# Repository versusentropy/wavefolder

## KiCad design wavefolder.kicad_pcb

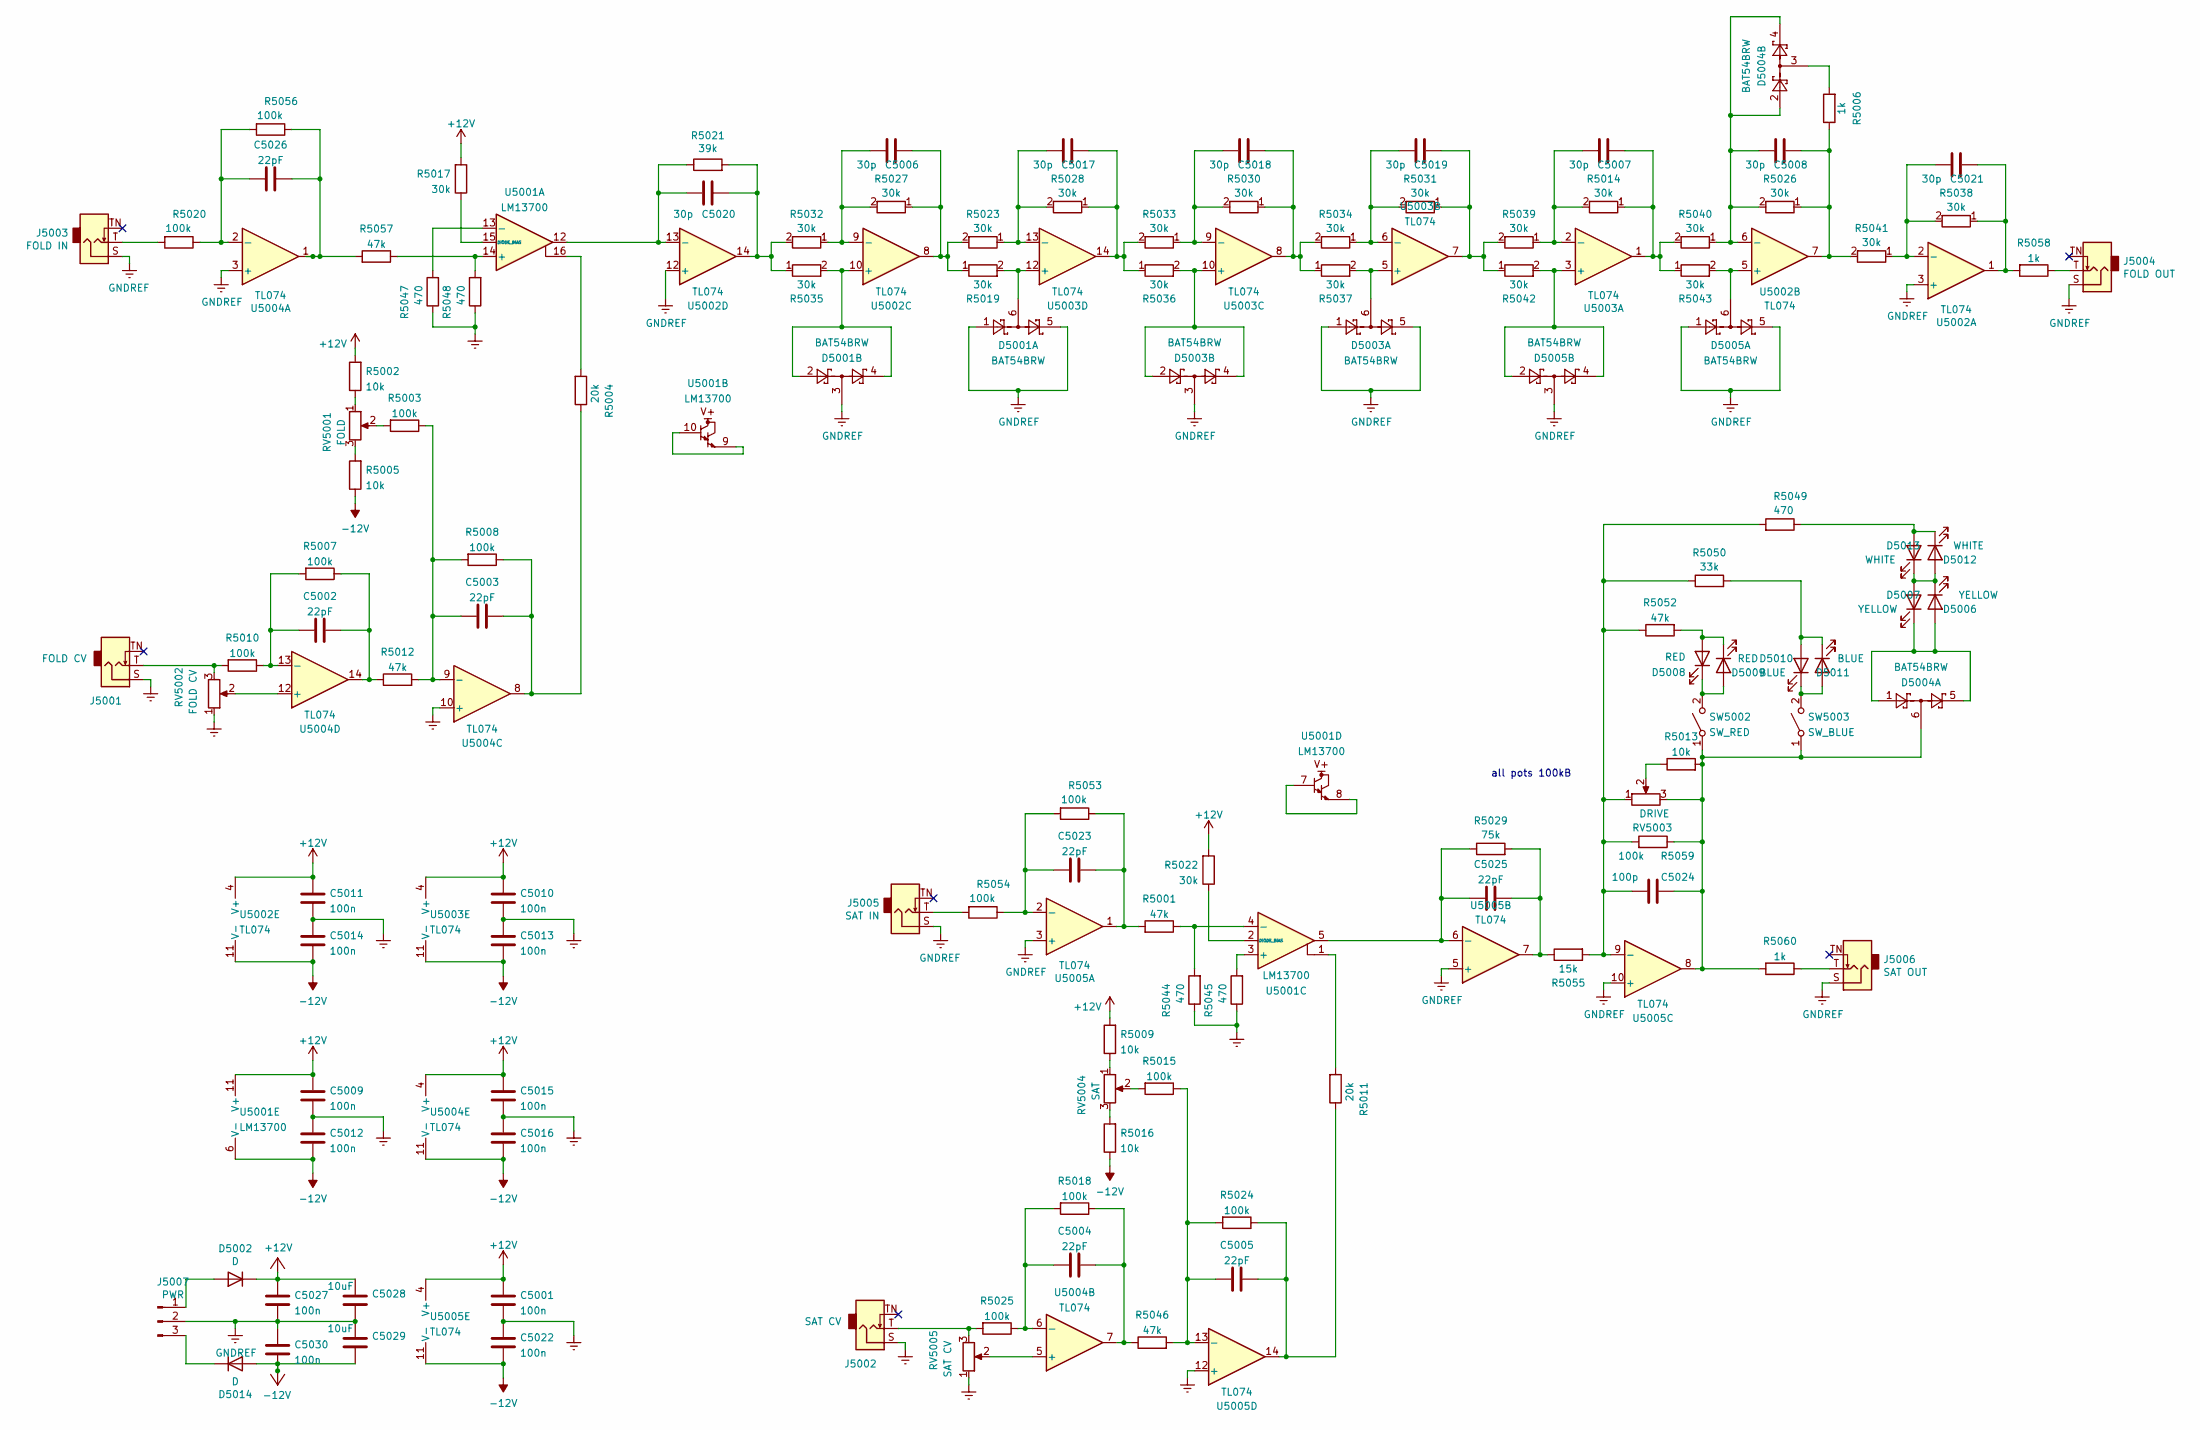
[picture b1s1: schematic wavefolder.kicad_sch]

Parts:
C5001, C5009, C5010, C5011, C5012, C5013, C5014, C5015, C5016, C5022, C5027, C5030: 100n; C_0402_1005Metric; LCSC C307331
C5002, C5003, C5004, C5005, C5023, C5025, C5026: 22pF; C_0402_1005Metric; LCSC C1555
C5006, C5007, C5008, C5017, C5018, C5019, C5020, C5021: 30p; C_0402_1005Metric; LCSC C1570
C5024: 100p; C_0402_1005Metric; LCSC C1546
C5028, C5029: 10uF; C_0805_2012Metric; LCSC C15850
D5001, D5003, D5004, D5005: BAT54BRW; SOT-363_SC-70-6; LCSC C124897
D5002, D5014: D; D_SOD-123; LCSC C8598
D5006, D5007: YELLOW; LED_D3.0mm
D5008, D5009: RED; LED_D3.0mm
D5010, D5011: BLUE; LED_D3.0mm
D5012, D5013: WHITE; LED_D3.0mm
J5001: FOLD CV; Jack_3.5mm_QingPu_WQP-PJ398SM_Vertical_CircularHolesSMALL
J5002: SAT CV; Jack_3.5mm_QingPu_WQP-PJ398SM_Vertical_CircularHolesSMALL
J5003: FOLD IN; Jack_3.5mm_QingPu_WQP-PJ398SM_Vertical_CircularHolesSMALL
J5004: FOLD OUT; Jack_3.5mm_QingPu_WQP-PJ398SM_Vertical_CircularHolesSMALL
J5005: SAT IN; Jack_3.5mm_QingPu_WQP-PJ398SM_Vertical_CircularHolesSMALL
J5006: SAT OUT; Jack_3.5mm_QingPu_WQP-PJ398SM_Vertical_CircularHolesSMALL
J5007: PWR; eurorac_power-v2
R5001, R5012, R5046, R5052, R5057: 47k; R_0402_1005Metric; LCSC C25792
R5002, R5005, R5009, R5013, R5016: 10k; R_0402_1005Metric; LCSC C25744
R5003, R5007, R5008, R5010, R5015, R5018, R5020, R5024, R5025, R5053, R5054, R5056, R5059: 100k; R_0402_1005Metric; LCSC C25741
R5004, R5011: 20k; R_0603_1608Metric; LCSC C4184
R5006, R5058, R5060: 1k; R_0603_1608Metric; LCSC C21190
R5014, R5017, R5019, R5022, R5023, R5026, R5027, R5028, R5030, R5031, R5032, R5033, R5034, R5035, R5036, R5037, R5038, R5039, R5040, R5041, R5042, R5043: 30k; R_0402_1005Metric; LCSC C141650
R5021: 39k; R_0402_1005Metric; LCSC C25783
R5029: 75k; R_0402_1005Metric; LCSC C25798
R5044, R5045, R5047, R5048, R5049: 470; R_0402_1005Metric; LCSC C25117
R5050: 33k; R_0402_1005Metric; LCSC C141650
R5055: 15k; R_0402_1005Metric; LCSC C25756
RV5001: FOLD; RD901F-ALPHA-POT
RV5002: FOLD CV; RD901F-ALPHA-POT
RV5003: DRIVE; RD901F-ALPHA-POT
RV5004: SAT; RD901F-ALPHA-POT
RV5005: SAT CV; RD901F-ALPHA-POT
SW5002: SW_RED; SW_SPDT_2_5mm
SW5003: SW_BLUE; SW_SPDT_2_5mm
U5001: LM13700; SOIC-16_3.9x9.9mm_P1.27mm; LCSC C174050
U5002, U5003, U5004, U5005: TL074; TSSOP-14_4.4x5mm_P0.65mm; LCSC C96507

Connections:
+12V: C5001.1, C5009.1, C5010.1, C5011.1, C5015.1, C5027.1, C5028.1, D5002.1 (K), R5002.2, R5009.2, R5017.2, R5022.2, U5001.11 (V+), U5002.4 (V+), U5003.4 (V+), U5004.4 (V+), U5005.4 (V+)
-12V: C5012.2, C5013.2, C5014.2, C5016.2, C5022.2, C5029.2, C5030.2, D5014.2 (A), R5005.1, R5016.1, U5001.6 (V-), U5002.11 (V-), U5003.11 (V-), U5004.11 (V-), U5005.11 (V-)
GNDREF: C5001.2, C5009.2, C5010.2, C5011.2, C5012.1, C5013.1, C5014.1, C5015.2, C5016.1, C5022.1, C5027.2, C5028.2, C5029.1, C5030.1, D5001.1, D5001.3, D5001.5, D5003.1, D5003.3, D5003.5, D5005.1, D5005.3, D5005.5, J5001.S, J5002.S, J5003.S, J5004.S, J5005.S, J5006.S, J5007.2, R5044.1, R5045.1, R5047.1, R5048.1, RV5002.1, RV5005.1, U5002.3 (+), U5002.12 (+), U5004.3 (+), U5004.10 (+), U5005.3 (+), U5005.5 (+), U5005.10 (+), U5005.12 (+)
unnamed: C5002.1, R5007.2, R5010.1, U5004.13 (-)
unnamed: C5002.2, R5007.1, R5012.1, U5004.14
unnamed: C5003.1, R5003.1, R5008.2, R5012.2, U5004.9 (-)
unnamed: C5003.2, R5004.1, R5008.1, U5004.8
unnamed: C5004.1, R5018.2, R5025.1, U5004.6 (-)
unnamed: C5004.2, R5018.1, R5046.1, U5004.7
unnamed: C5005.1, R5015.1, R5024.2, R5046.2, U5005.13 (-)
unnamed: C5005.2, R5011.1, R5024.1, U5005.14
unnamed: C5006.1, R5019.1, R5023.2, R5027.1, U5002.8
unnamed: C5006.2, R5027.2, R5032.1, U5002.9 (-)
unnamed: C5007.1, R5014.1, R5040.2, R5043.1, U5003.1
unnamed: C5007.2, R5014.2, R5039.1, U5003.2 (-)
unnamed: C5008.1, R5006.1, R5026.1, R5041.2, U5002.7
unnamed: C5008.2, D5004.2, D5004.4, R5026.2, R5040.1, U5002.6 (-)
unnamed: C5017.1, R5028.1, R5033.2, R5036.1, U5003.14
unnamed: C5017.2, R5023.1, R5028.2, U5003.13 (-)
unnamed: C5018.1, R5030.1, R5034.2, R5037.1, U5003.8
unnamed: C5018.2, R5030.2, R5033.1, U5003.9 (-)
unnamed: C5019.1, R5031.1, R5039.2, R5042.1, U5003.7
unnamed: C5019.2, R5031.2, R5034.1, U5003.6 (-)
unnamed: C5020.1, R5021.2, R5032.2, R5035.1, U5002.14
unnamed: C5020.2, R5021.1, U5001.12, U5002.13 (-)
unnamed: C5021.1, R5038.1, R5058.2, U5002.1
unnamed: C5021.2, R5038.2, R5041.1, U5002.2 (-)
unnamed: C5023.1, R5053.2, R5054.1, U5005.2 (-)
unnamed: C5023.2, R5001.2, R5053.1, U5005.1
unnamed: C5024.1, D5004.6, R5013.2, R5059.1, R5060.2, RV5003.3, SW5002.1 (A), SW5003.1 (A), U5005.8
unnamed: C5024.2, R5049.2, R5050.1, R5052.1, R5055.2, R5059.2, RV5003.1, U5005.9 (-)
unnamed: C5025.1, R5029.1, U5001.5, U5005.6 (-)
unnamed: C5025.2, R5029.2, R5055.1, U5005.7
unnamed: C5026.1, R5020.1, R5056.2, U5004.2 (-)
unnamed: C5026.2, R5056.1, R5057.2, U5004.1
unnamed: D5001.2, D5001.4, R5035.2, U5002.10 (+)
unnamed: D5001.6, R5019.2, U5003.12 (+)
unnamed: D5002.2 (A), J5007.1
unnamed: D5003.2, D5003.4, R5036.2, U5003.10 (+)
unnamed: D5003.6, R5037.2, U5003.5 (+)
unnamed: D5004.1, D5004.5, D5006.2 (A), D5007.1 (K)
unnamed: D5004.3, R5006.2
unnamed: D5005.2, D5005.4, R5042.2, U5003.3 (+)
unnamed: D5005.6, R5043.2, U5002.5 (+)
unnamed: D5006.1 (K), D5007.2 (A), D5012.2 (A), D5013.1 (K)
unnamed: D5008.1 (K), D5009.2 (A), SW5002.2 (B)
unnamed: D5008.2 (A), D5009.1 (K), R5052.2
unnamed: D5010.1 (K), D5011.2 (A), SW5003.2 (B)
unnamed: D5010.2 (A), D5011.1 (K), R5050.2
unnamed: D5012.1 (K), D5013.2 (A), R5049.1
unnamed: D5014.1 (K), J5007.3
unnamed: J5001.T, R5010.2, RV5002.3
unnamed: J5002.T, R5025.2, RV5005.3
unnamed: J5003.T, R5020.2
unnamed: J5004.T, R5058.1
unnamed: J5005.T, R5054.2
unnamed: J5006.T, R5060.1
unnamed: R5001.1, R5044.2, U5001.4 (-)
unnamed: R5002.1, RV5001.1
unnamed: R5003.2, RV5001.2
unnamed: R5004.2, U5001.16
unnamed: R5005.2, RV5001.3
unnamed: R5009.1, RV5004.1
unnamed: R5011.2, U5001.1
unnamed: R5013.1, RV5003.2
unnamed: R5015.2, RV5004.2
unnamed: R5016.2, RV5004.3
unnamed: R5017.1, U5001.15 (DIODE_BIAS)
unnamed: R5022.1, U5001.2 (DIODE_BIAS)
unnamed: R5045.2, U5001.3 (+)
unnamed: R5047.2, U5001.13 (-)
unnamed: R5048.2, R5057.1, U5001.14 (+)
unnamed: RV5002.2, U5004.12 (+)
unnamed: RV5005.2, U5004.5 (+)
unnamed: U5001.7, U5001.8
unnamed: U5001.9, U5001.10

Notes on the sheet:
all pots 100kB

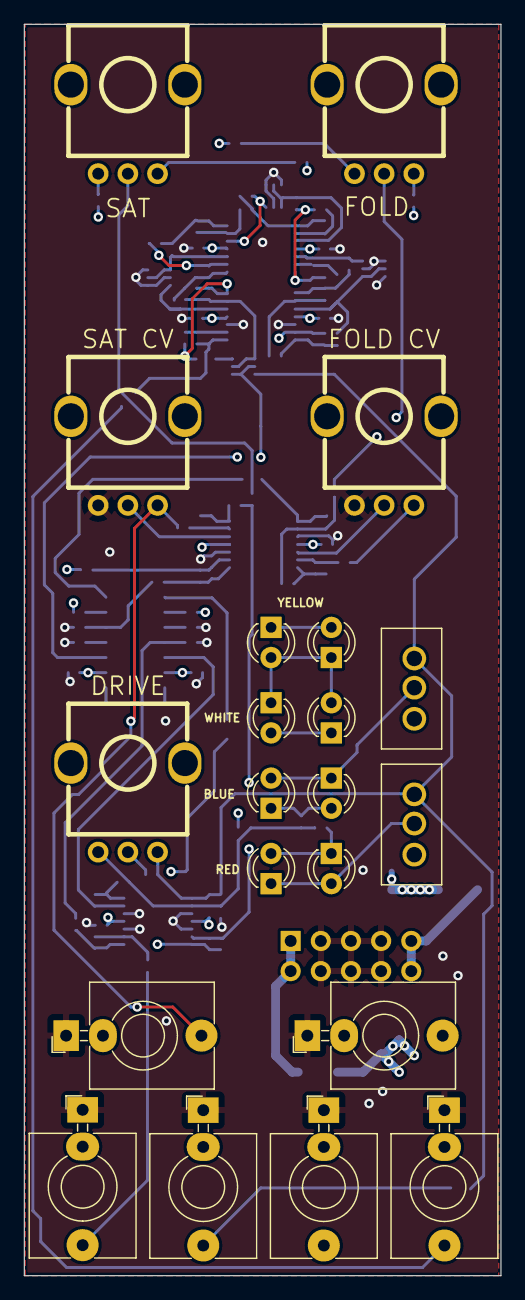
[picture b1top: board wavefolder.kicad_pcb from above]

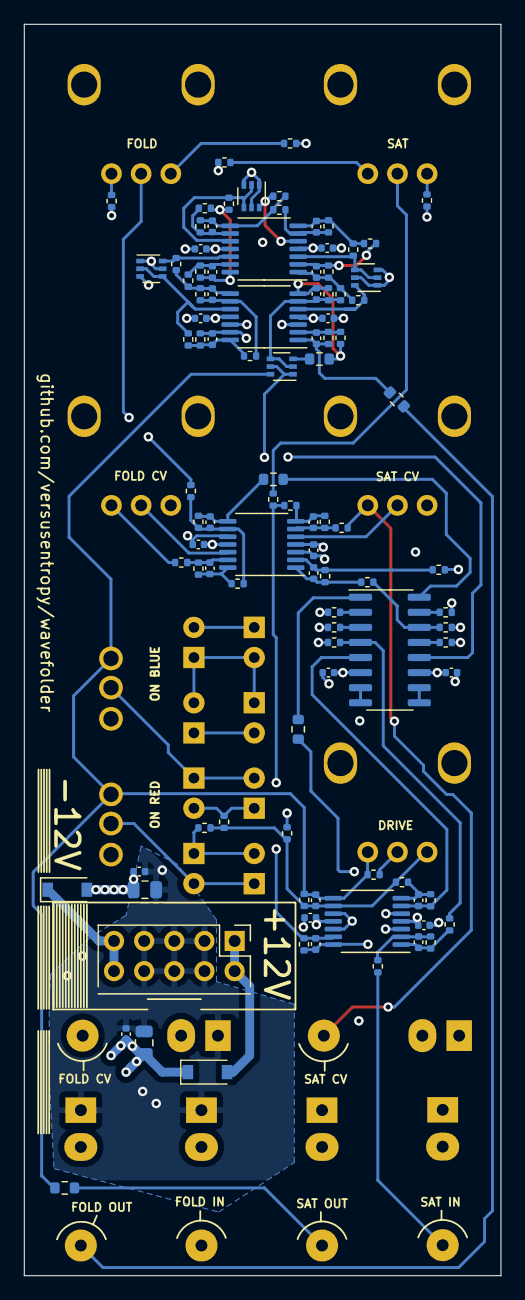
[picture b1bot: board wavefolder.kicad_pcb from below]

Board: 4 copper layers, 40.1 x 105.4 mm, 122 parts (101 on the bottom side), 76 nets.

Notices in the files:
wavefolder.kicad_pcb:
CC BY-SA-NC 4.0
